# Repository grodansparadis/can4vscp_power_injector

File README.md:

<h1>Power injector module for CAN4VSCP</h1>

With the power injector you can power the CAN4VSCP bus and also power up to 16 CAN4VSCP modules using the daisy chain connector. This is a perfect companion board to use when you need to connect a number of CAN4VSCP boards in a cabinet and then connect them to thw world.

It also have two 120 ohm terminations that can be activated if needed.

It is also possible to get the module with a resettable fuse that allow a maximum of 500 mA for all modules connected to the board. The fuse will trip at about 800 mA. This can be a good safety precaution for wired networks. 

<hr>

This project is part of the <a href="http://www.vscp.org">VSCP (Very Simple Control Protocol) project</a>. 

<hr>

This project is licensed under the 
<a href="http://creativecommons.org/licenses/by-nc-sa/3.0/">Creative Commons open source license Attribution-NonCommercial-ShareAlike 3.0 Unported</a>. 
Other license options are available by conacting <a href="malto:info@grodansparadis.com">Paradis of the Frog AB</a>

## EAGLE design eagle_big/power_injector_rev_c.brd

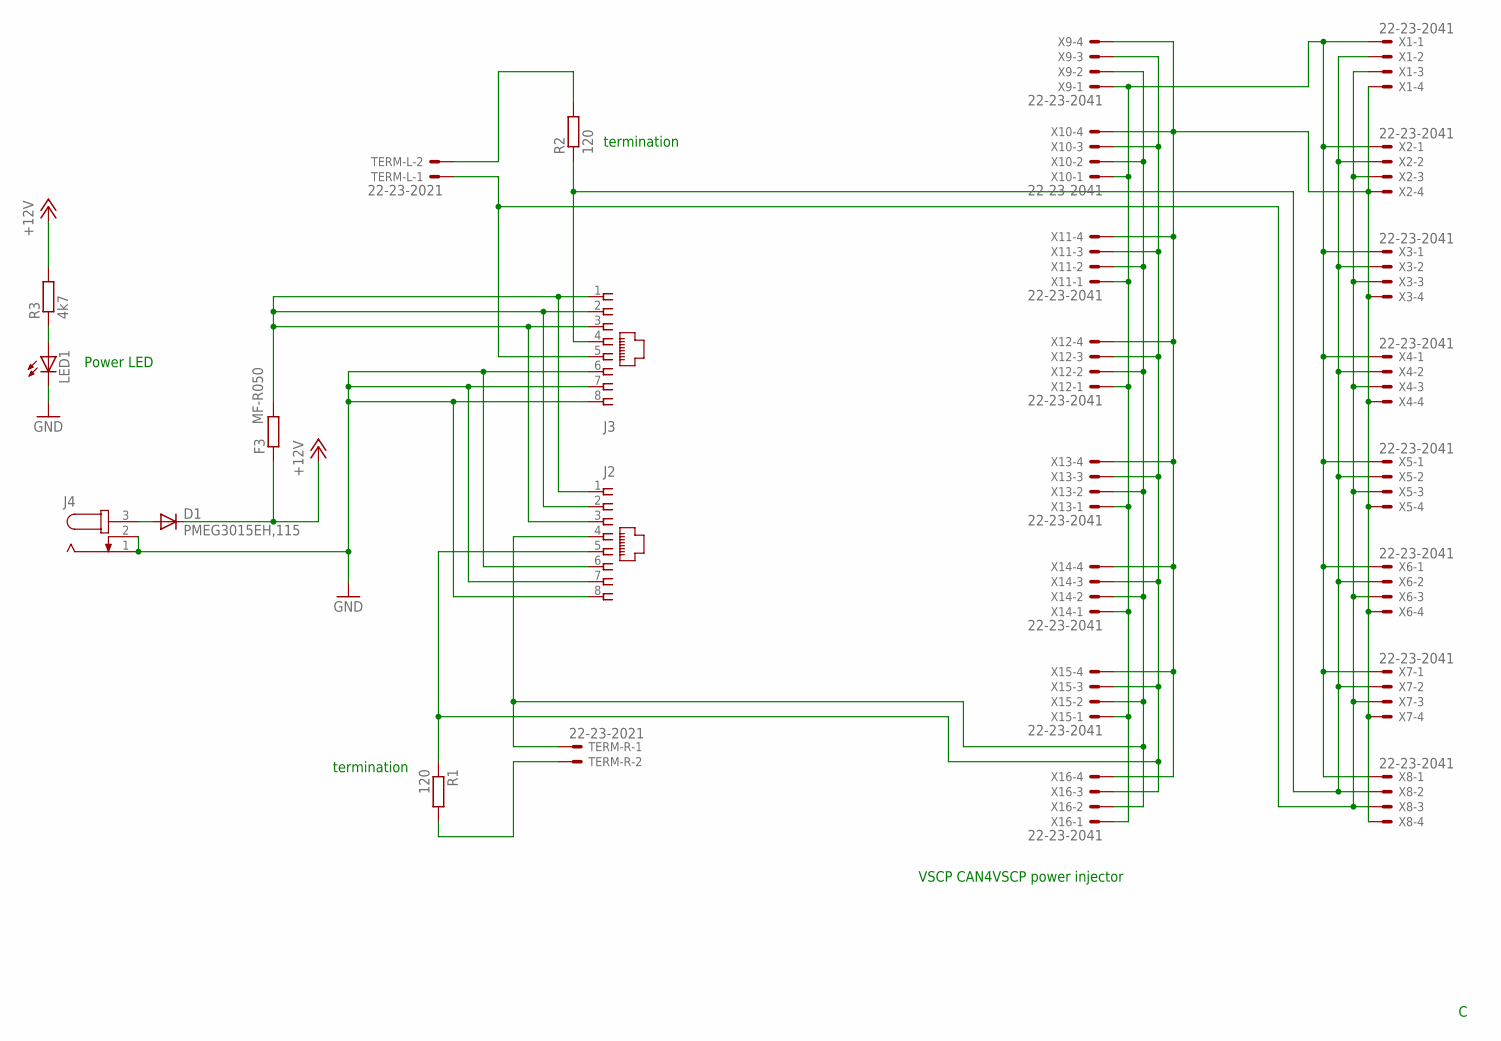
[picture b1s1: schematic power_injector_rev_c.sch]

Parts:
D1: PMEG3015EH,115; SMB
F3: MF-R050; 0204/5
J2, J3: A00-108-220-450; RJ-45
J4: JACK-PLUG0; SPC4077
LED1: LEDCHIP-LED0805; CHIP-LED0805
R1, R2: 120; R0805
R3: 4k7; R0805
TERM-L: 22-23-2021
TERM-R: 22-23-2021
X1, X2, X3, X4, X5, X6, X7, X8, X9, X10, X11, X12, X13, X14, X15, X16: 22-23-2041

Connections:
+12V: D1.C, F3.1, R3.2
CANH: J2.4, J3.4, R2.1, TERM-R.1, X1.2, X2.2, X3.2, X4.2, X5.2, X6.2, X7.2, X8.2, X9.2, X10.2, X11.2, X12.2, X13.2, X14.2, X15.2, X16.2
CANL: J2.5, J3.5, R1.1, TERM-L.1, X1.3, X2.3, X3.3, X4.3, X5.3, X6.3, X7.3, X8.3, X9.3, X10.3, X11.3, X12.3, X13.3, X14.3, X15.3, X16.3
GND: J2.6, J2.7, J2.8, J3.6, J3.7, J3.8, J4.1, J4.2, LED1.C, X1.4, X2.4, X3.4, X4.4, X5.4, X6.4, X7.4, X8.4, X9.4, X10.4, X11.4, X12.4, X13.4, X14.4, X15.4, X16.4
unnamed: LED1.A, R3.1
unnamed: R1.2, TERM-R.2
unnamed: D1.A, J4.3
unnamed: R2.2, TERM-L.2
POWER: F3.2, J2.1, J2.2, J2.3, J3.1, J3.2, J3.3, X1.1, X2.1, X3.1, X4.1, X5.1, X6.1, X7.1, X8.1, X9.1, X10.1, X11.1, X12.1, X13.1, X14.1, X15.1, X16.1

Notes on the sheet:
Power LED
VSCP CAN4VSCP power injector
termination

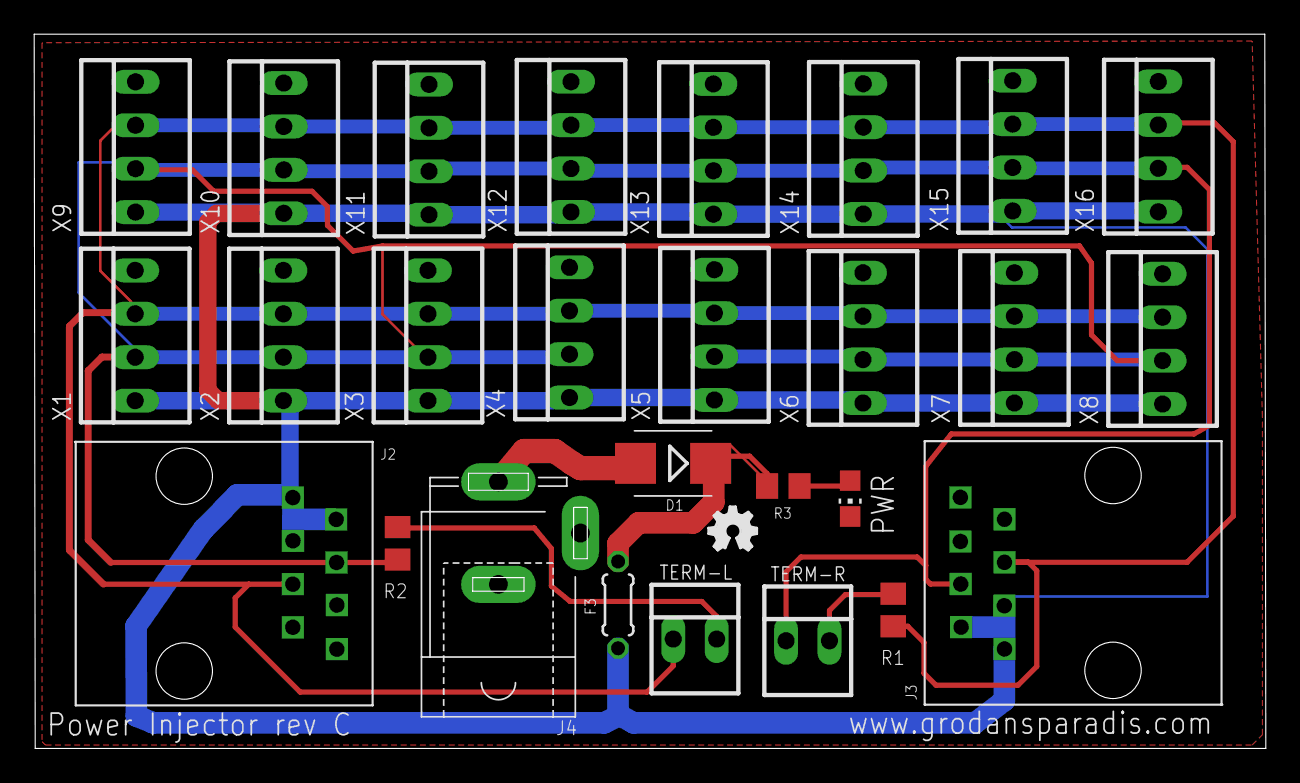
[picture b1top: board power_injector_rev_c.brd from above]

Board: 2 copper layers, 72.1 x 41.8 mm, 28 parts (0 on the bottom side), 9 nets.

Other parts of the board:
U$1: OSHW_FILLX100_NOTEXT

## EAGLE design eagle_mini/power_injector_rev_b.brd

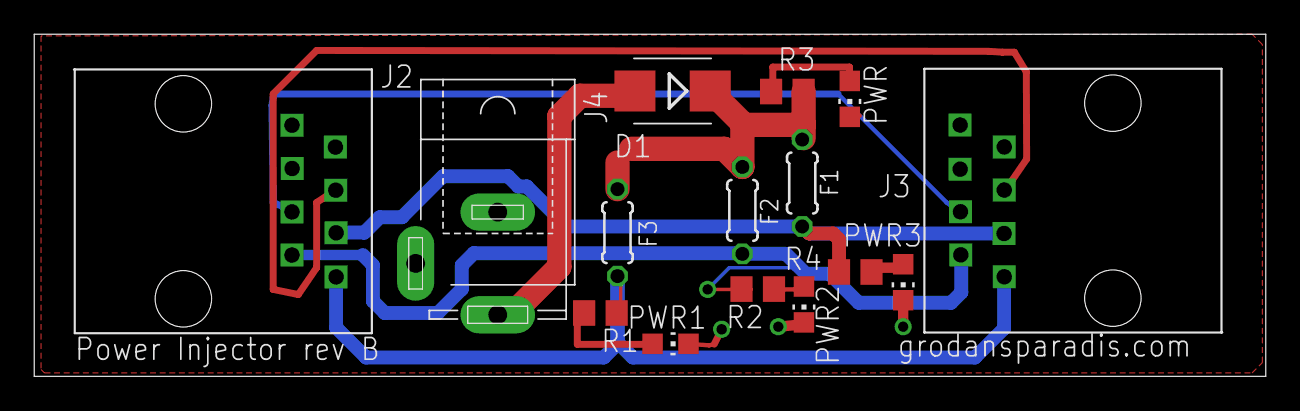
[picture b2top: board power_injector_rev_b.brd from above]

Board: 2 copper layers, 72.0 x 20.0 mm, 15 parts (0 on the bottom side), 12 nets.

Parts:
D1: S1D; SMB
F1, F2, F3: MF-R050; 0204/5
J2, J3: A00-108-220-450; RJ-45
J4: SPC4077
LED1, LED2, LED3, LED4: CHIP-LED0805
R1, R2, R3, R4: 4k7; R0805

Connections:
+12V: D1.C, F1.1, F2.1, F3.1, R3.2
GND: J2.1, J2.2, J2.3, J3.6, J3.7, J3.8, J4.1, J4.2, LED1.C, LED2.C, LED3.C, LED4.C
unnamed: LED3.A, R2.1
unnamed: LED1.A, R3.1
unnamed: J2.5, J3.4
unnamed: J2.4, J3.5
unnamed: LED4.A, R4.1
unnamed: LED2.A, R1.1
unnamed: D1.A, J4.3
PWR1: F3.2, J2.8, J3.1, R1.2
PWR2: F2.2, J2.7, J3.2, R2.2
PWR3: F1.2, J2.6, J3.3, R4.2

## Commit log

2015-08-29 Added new design
2015-09-02 Added board and schema pictures
2015-09-28 Added terminators and changed connection sequence
2015-11-22 Edit + bom added + gerbers
2015-12-17 Updated license
2015-12-22 Named D1
